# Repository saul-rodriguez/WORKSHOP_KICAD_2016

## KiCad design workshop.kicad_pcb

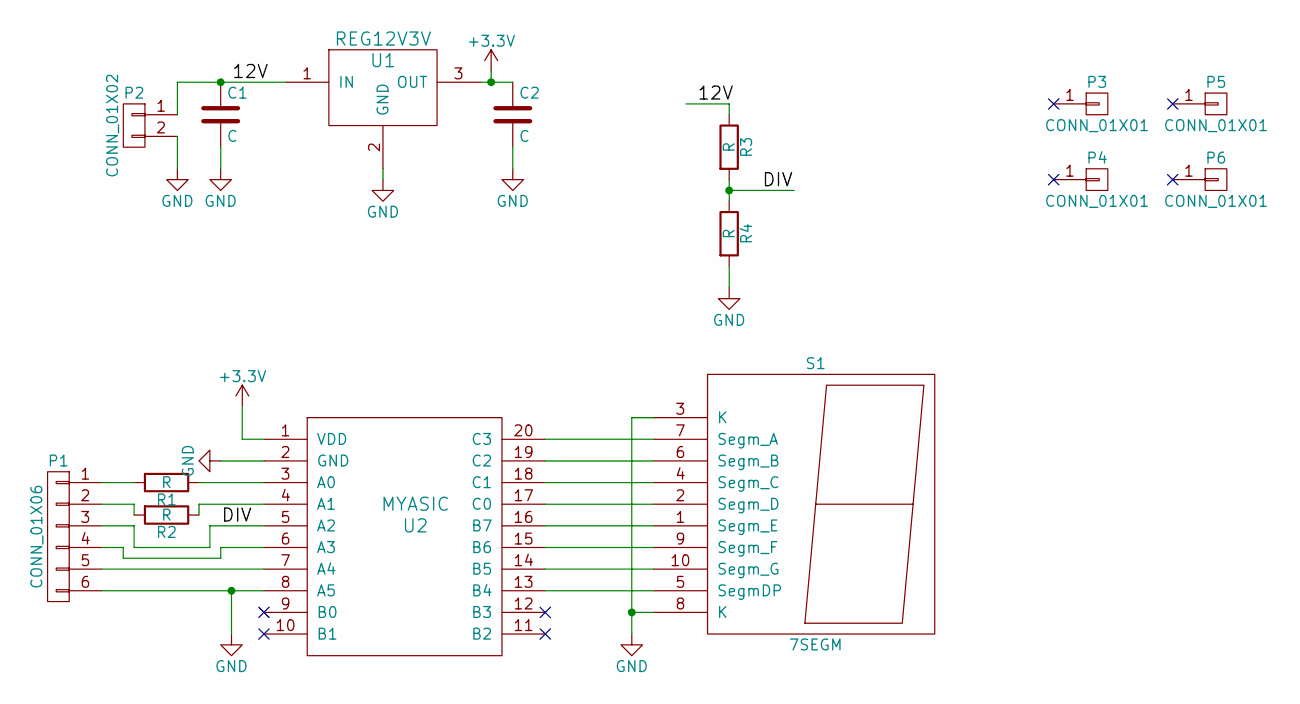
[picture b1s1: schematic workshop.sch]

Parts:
C1: C; C_Radial_D5_L11_P2
C2: C; C_Disc_D7.5_P5
P1: CONN_01X06; Pin_Header_Straight_1x06
P2: CONN_01X02; Pin_Header_Straight_1x02
P3, P4, P5, P6: CONN_01X01; MountingHole_3.5mm_Pad
R1, R2: R; R_0402
R3, R4: R; Resistor_Horizontal_RM10mm
S1: 7SEGM; 7SegmentLED_LTS6760_LTS6780
U1: REG12V3V; SC-70
U2: MYASIC; plcc20_pth-skt

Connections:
+3V3: C2.1, U1.3 (OUT), U2.1 (VDD)
/12V: C1.1, P2.1, R3.1, U1.1 (IN)
/DIV: P1.3, R3.2, R4.1, U2.5 (A2)
GND: C1.2, C2.2, P1.6, P2.2, R4.2, S1.3 (K), S1.8 (K), U1.2 (GND), U2.2 (GND), U2.8 (A5)
unnamed: P1.1, R1.2
unnamed: P1.2, R2.2
unnamed: P1.4, U2.6 (A3)
unnamed: P1.5, U2.7 (A4)
unnamed: R1.1, U2.3 (A0)
unnamed: R2.1, U2.4 (A1)
unnamed: S1.1 (Segm_E), U2.16 (B7)
unnamed: S1.2 (Segm_D), U2.17 (C0)
unnamed: S1.4 (Segm_C), U2.18 (C1)
unnamed: S1.5 (SegmDP), U2.13 (B4)
unnamed: S1.6 (Segm_B), U2.19 (C2)
unnamed: S1.7 (Segm_A), U2.20 (C3)
unnamed: S1.9 (Segm_F), U2.15 (B6)
unnamed: S1.10 (Segm_G), U2.14 (B5)

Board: 4 copper layers, 15 parts (0 on the bottom side), 18 nets, no tracks yet.
